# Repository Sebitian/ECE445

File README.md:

# Smart Bike Lock System (Secured Illini)

Embedded IoT system for real-time bike security, combining Bluetooth authentication, motion-based tamper detection, and cloud monitoring. Designed and built as a full-stack hardware + firmware solution with a custom PCB, power subsystem, and multi-state control architecture.

---

## Overview

This project addresses the limitations of traditional bike locks by introducing a multi-layered smart security system. The device enables keyless locking via Bluetooth, detects unauthorized motion using onboard sensors, and sends real-time alerts to a cloud dashboard.

The system integrates embedded firmware, wireless communication, and physical hardware design into a single cohesive product.

---

## Key Features

- Bluetooth Low Energy (BLE) locking/unlocking
- Motion-based tamper detection using IMU (MPU6050)
- Finite State Machine (LOCKED, UNLOCKED, ALARM)
- Real-time cloud monitoring via ThingSpeak
- Servo-actuated locking mechanism
- Audible alarm + LED alert system
- Custom PCB with integrated power and control subsystems
- End-to-end system from hardware to cloud

---

## System Architecture

### Hardware
- ESP32-S3 microcontroller
- MPU6050 accelerometer/gyroscope
- Servo motor (locking mechanism)
- Piezo buzzer (alarm system)
- Custom-designed PCB
- 4.8V 2000mAh battery + 3.3V regulation (LM1117)

### Software
- Embedded C++ (Arduino framework)
- BLE server with custom services and callbacks
- HTTP-based cloud communication (ThingSpeak)
- Real-time state management using FSM

---

## Finite State Machine

The system is controlled by a 3-state FSM:

- **LOCKED**
  - Default state
  - Monitors acceleration for tampering
  - Triggers ALARM when threshold exceeded

- **UNLOCKED**
  - Triggered via authenticated BLE command
  - Disables motion-based alerts

- **ALARM**
  - Triggered on suspicious motion
  - Activates buzzer + LED flashing
  - Sends periodic cloud updates until reset

State transitions are driven by both user commands and sensor input.

---

## Motion Detection Algorithm

Tampering is detected using acceleration magnitude computed from IMU data:

- Combines x, y, z acceleration using Euclidean norm
- Adjusts for gravity (~9.8 m/s²)
- Triggers alarm when threshold exceeds ~13 m/s²

This approach enables robust detection of real-world disturbances while filtering noise.

---

## Cloud Monitoring

- Data sent via HTTP POST to ThingSpeak
- Logged data includes:
  - Lock state (LOCKED / UNLOCKED / ALARM)
  - Temperature
  - Acceleration (x, y, z)

**Performance:**
- Alert latency: ~22 seconds from tamper event to dashboard update
- Continuous updates every 15 seconds during alarm state

---

## Performance & Testing

- Lock/unlock response time: ~1.5 seconds via BLE  
- Reliable motion detection using threshold-based IMU analysis  
- Real-time alert system validated through live testing  
- Estimated battery life:
  - ~2.3 days (passive)
  - Higher under optimized conditions  

---

## Engineering Challenges

- Initial PCB revisions lacked proper USB-UART connections
- Stepper motor limitations required redesign → switched to servo
- Debugging soldering and signal integrity issues under ESP32
- BLE + WiFi integration timing and reliability

---

## Solutions

- Redesigned PCB with correct USB bridge integration
- Transitioned to servo motor for precise control
- Iterative debugging and hardware refinement
- Optimized firmware for stable communication and control

---

## Future Improvements

- Mobile application for improved user experience
- GPS tracking for stolen bike recovery
- Push notifications instead of dashboard polling
- Power optimization for extended battery life
- Modular smart attachment for existing locks

---

## Team

- Sebastian Sovailescu  
- Andrew Ruiz  
- Bowen Cui  

University of Illinois Urbana-Champaign  
ECE 445 – Senior Design

---

## Summary

This project demonstrates the design and implementation of a complete embedded system integrating hardware, firmware, and cloud infrastructure. It highlights real-world engineering challenges, iterative development, and system-level thinking in building a practical IoT security device.

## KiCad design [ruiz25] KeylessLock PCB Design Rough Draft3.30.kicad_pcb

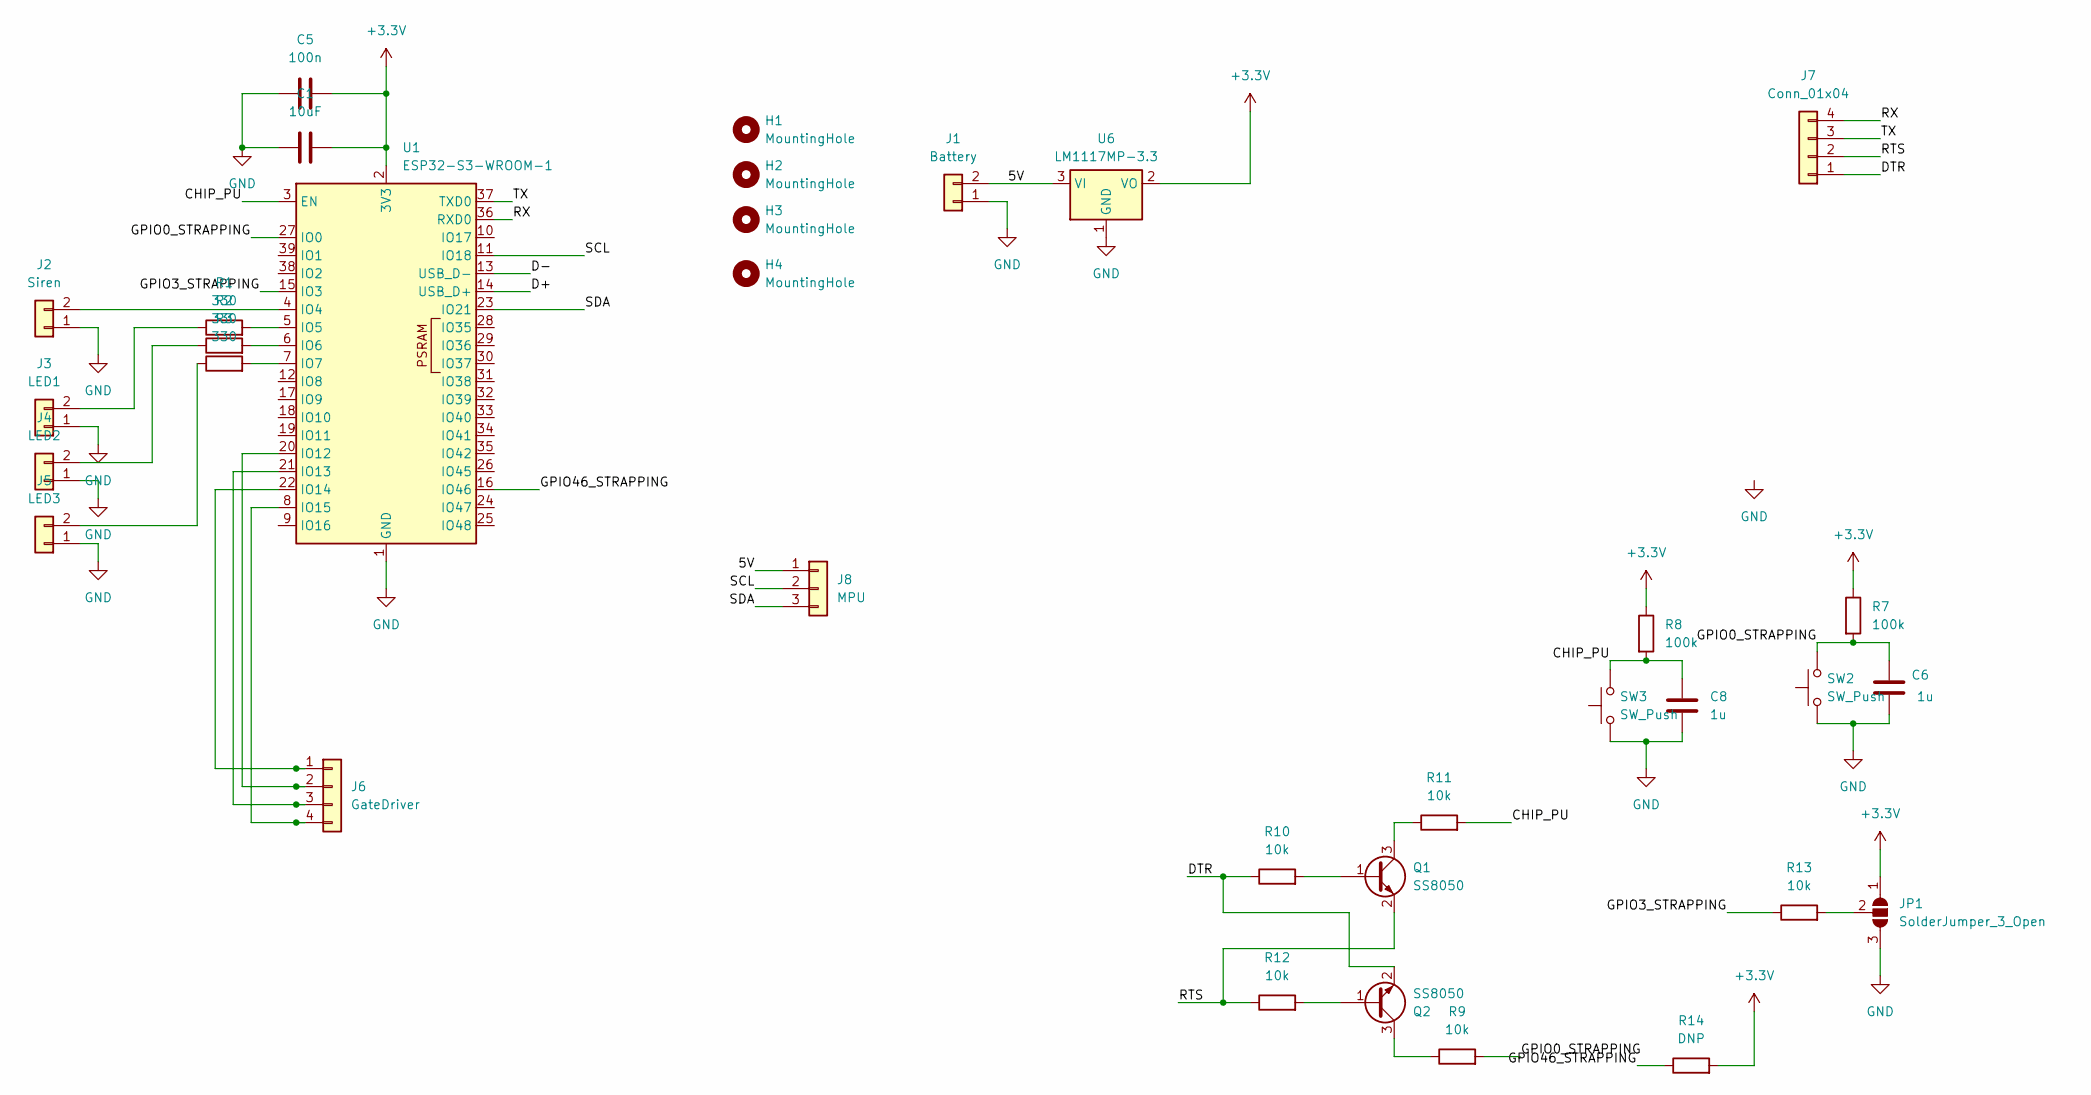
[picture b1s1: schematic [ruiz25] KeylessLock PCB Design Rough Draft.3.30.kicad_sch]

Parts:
C1: 10uF; C_0805_2012Metric_Pad1.18x1.45mm_HandSolder
C5: 100n; C_0805_2012Metric_Pad1.18x1.45mm_HandSolder
C6, C8: 1u; C_0805_2012Metric_Pad1.18x1.45mm_HandSolder
H1, H2, H3, H4: MountingHole; MountingHole_3.2mm_M3
J1: Battery; Molex_KK-254_AE-6410-02A_1x02_P2.54mm_Vertical
J2: Siren; Molex_KK-254_AE-6410-02A_1x02_P2.54mm_Vertical
J3: LED1; Molex_KK-254_AE-6410-02A_1x02_P2.54mm_Vertical
J4: LED2; Molex_KK-254_AE-6410-02A_1x02_P2.54mm_Vertical
J5: LED3; Molex_KK-254_AE-6410-02A_1x02_P2.54mm_Vertical
J6: GateDriver; Molex_KK-254_AE-6410-04A_1x04_P2.54mm_Vertical
J7: Conn_01x04; Molex_KK-254_AE-6410-04A_1x04_P2.54mm_Vertical
J8: MPU; Molex_KK-254_AE-6410-03A_1x03_P2.54mm_Vertical
JP1: SolderJumper_3_Open; R_0805_2012Metric_Pad1.20x1.40mm_HandSolder
Q1, Q2: SS8050; SOT-23
R1, R2, R3: 330; R_0805_2012Metric_Pad1.20x1.40mm_HandSolder
R7, R8: 100k; R_0805_2012Metric_Pad1.20x1.40mm_HandSolder
R9, R10, R11, R12, R13: 10k; R_0805_2012Metric_Pad1.20x1.40mm_HandSolder
R14: DNP; R_0805_2012Metric_Pad1.20x1.40mm_HandSolder
SW2, SW3: SW_Push; SW_PUSH_6mm
U1: ESP32-S3-WROOM-1
U6: LM1117MP-3.3; SOT-223-3_TabPin2

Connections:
+3.3V: C1.2, C5.2, JP1.1 (A), R7.1, R8.1, R14.2, U1.2 (3V3), U6.2 (VO)
/5V: J1.2, J8.1, U6.3 (VI)
/CHIP_PU: C8.1, R8.2, R11.2, SW3.2, U1.3 (EN)
/D+: U1.14 (USB_D+)
/D-: U1.13 (USB_D-)
/DTR: J7.1, Q2.2 (E), R10.1
/GPIO0_STRAPPING: C6.1, R7.2, R9.2, SW2.2, U1.27 (IO0)
/GPIO3_STRAPPING: R13.1, U1.15 (IO3)
/GPIO46_STRAPPING: R14.1, U1.16 (IO46)
/RTS: J7.2, Q1.2 (E), R12.1
/RX: J7.4, U1.36 (RXD0)
/SCL: J8.2, U1.11 (IO18)
/SDA: J8.3, U1.23 (IO21)
/TX: J7.3, U1.37 (TXD0)
GND: C1.1, C5.1, C6.2, C8.2, J1.1, J2.1, J3.1, J4.1, J5.1, JP1.3 (B), SW2.1, SW3.1, U1.1 (GND), U1.40 (GND), U1.41 (GND), U6.1 (GND)
unnamed: J2.2, U1.4 (IO4)
unnamed: J3.2, R1.1
unnamed: J4.2, R2.1
unnamed: J5.2, R3.1
unnamed: J6.1, U1.22 (IO14)
unnamed: J6.2, U1.20 (IO12)
unnamed: J6.3, U1.21 (IO13)
unnamed: J6.4, U1.8 (IO15)
unnamed: JP1.2 (C), R13.2
unnamed: Q1.1 (B), R10.2
unnamed: Q1.3 (C), R11.1
unnamed: Q2.1 (B), R12.2
unnamed: Q2.3 (C), R9.1
unnamed: R1.2, U1.5 (IO5)
unnamed: R2.2, U1.6 (IO6)
unnamed: R3.2, U1.7 (IO7)

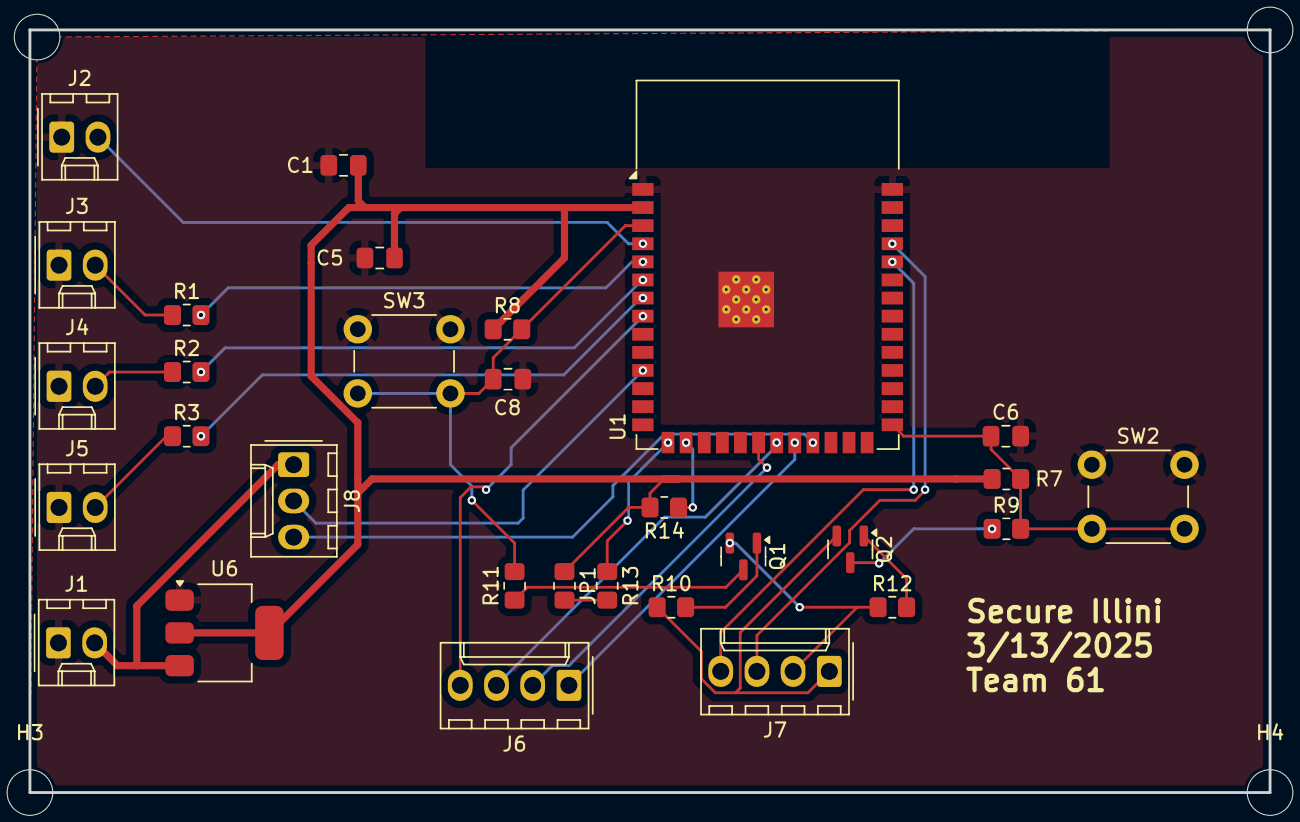
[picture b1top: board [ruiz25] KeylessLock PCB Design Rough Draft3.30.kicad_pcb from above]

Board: 2 copper layers, 87.0 x 53.5 mm, 34 parts (0 on the bottom side), 29 nets.

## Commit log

2025-03-02 Add files via upload
    Routing done, not optimised fine enough for first turn in
2026-04-15 Revise README with project details and features
    Updated project description and added detailed sections on system architecture, features, performance, and future improvements.
